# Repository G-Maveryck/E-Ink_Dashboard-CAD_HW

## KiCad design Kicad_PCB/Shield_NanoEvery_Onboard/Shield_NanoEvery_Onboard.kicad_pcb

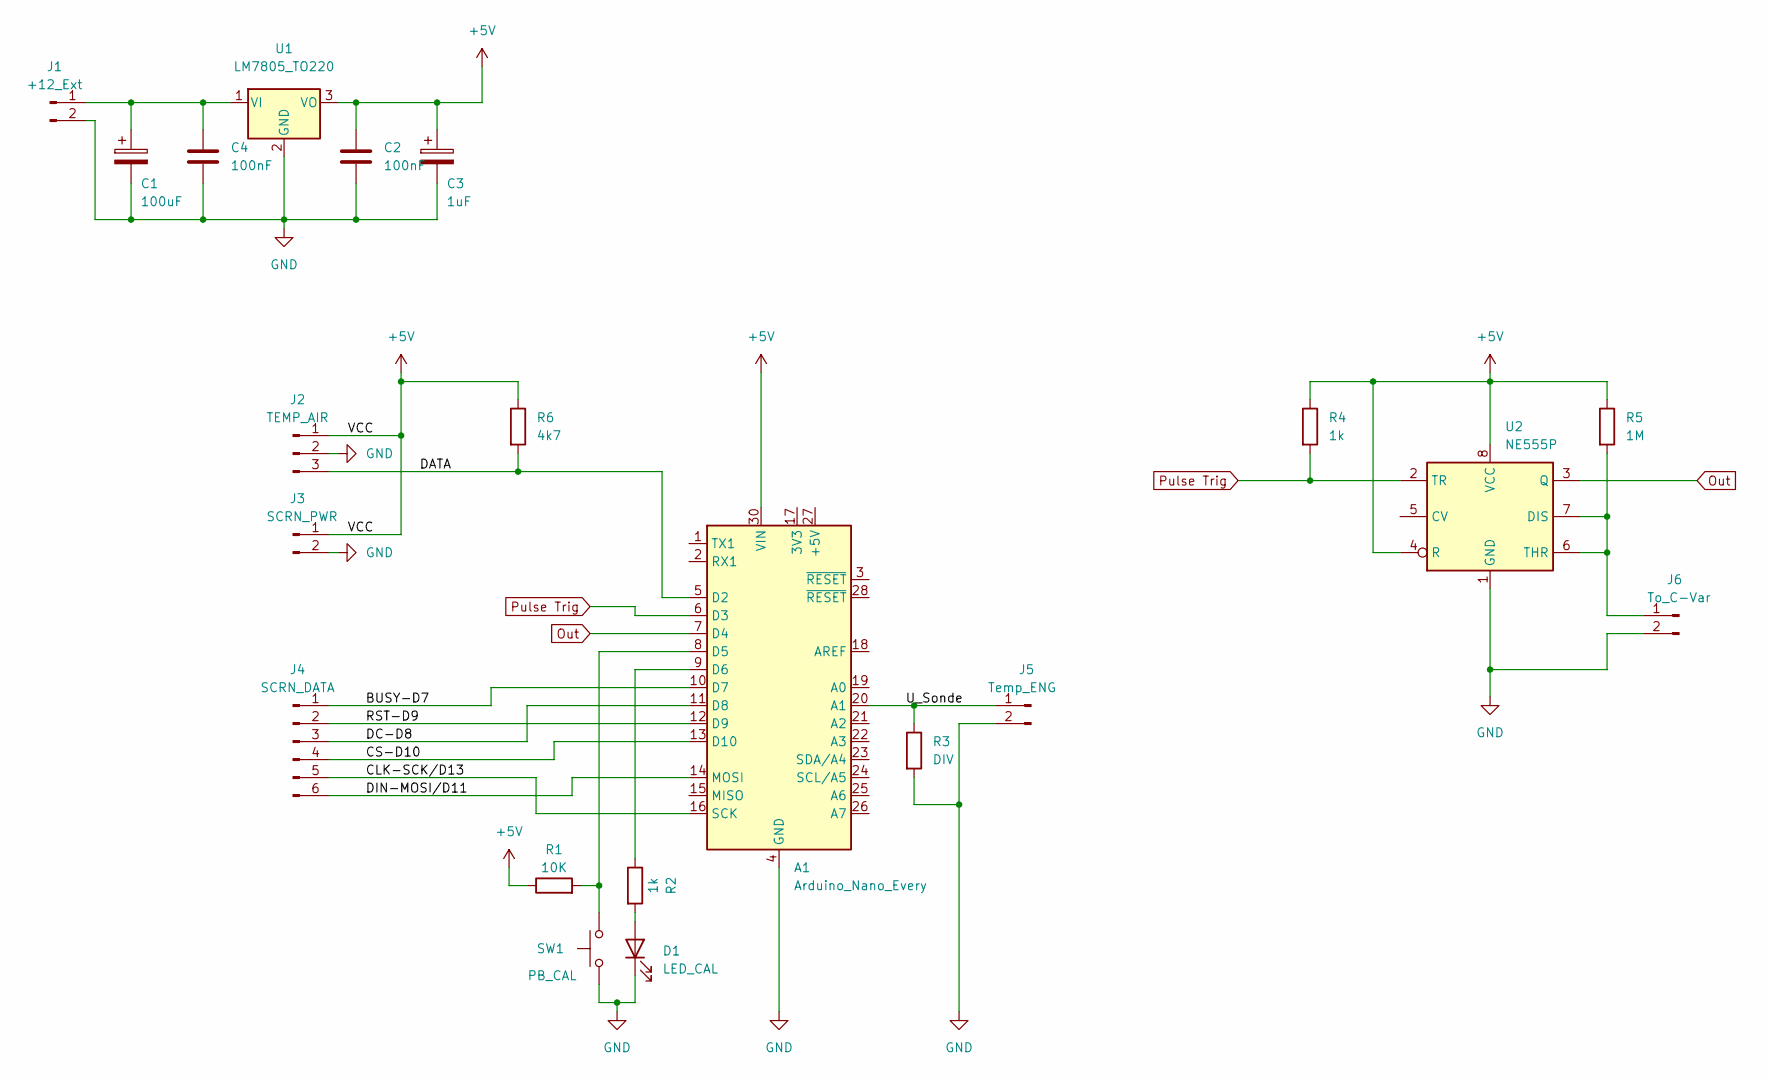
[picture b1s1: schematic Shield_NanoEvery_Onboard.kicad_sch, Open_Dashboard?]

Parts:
A1: Arduino_Nano_Every; Arduino_Nano
C1: 100uF; CP_Radial_D7.5mm_P2.50mm
C2, C4: 100nF; C_Disc_D4.3mm_W1.9mm_P5.00mm
C3: 1uF; CP_Radial_D5.0mm_P2.50mm
D1: LED_CAL; LED_D3.0mm
J1: +12_Ext; PinHeader_1x02_P2.54mm_Vertical
J2: TEMP_AIR; PinHeader_1x03_P2.54mm_Vertical
J3: SCRN_PWR; PinHeader_1x02_P2.54mm_Vertical
J4: SCRN_DATA; PinHeader_1x06_P2.54mm_Vertical
J5: Temp_ENG; PinHeader_1x02_P2.54mm_Vertical
J6: To_C-Var; PinHeader_1x02_P2.54mm_Vertical
R1: 10K; R_Axial_DIN0207_L6.3mm_D2.5mm_P7.62mm_Horizontal
R2, R4: 1k; R_Axial_DIN0207_L6.3mm_D2.5mm_P7.62mm_Horizontal
R3: DIV; R_Axial_DIN0207_L6.3mm_D2.5mm_P7.62mm_Horizontal
R5: 1M; R_Axial_DIN0207_L6.3mm_D2.5mm_P7.62mm_Horizontal
R6: 4k7; R_Axial_DIN0207_L6.3mm_D2.5mm_P7.62mm_Horizontal
SW1: PB_CAL; SW_PUSH_6mm_H4.3mm
U1: LM7805_TO220; TO-220-3_Vertical
U2: NE555P; DIP-8_W7.62mm

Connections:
+5V: A1.30 (VIN), C2.1, C3.1, J2.1, J3.1, R1.1, R4.1, R5.1, R6.1, U1.3 (VO), U2.4 (R), U2.8 (VCC)
/BUSY-D7: A1.10 (D7), J4.1
/CLK-SCK/D13: A1.16 (SCK), J4.5
/CS-D10: A1.13 (D10), J4.4
/DATA: A1.5 (D2), J2.3, R6.2
/DC-D8: A1.11 (D8), J4.3
/DIN-MOSI/D11: A1.14 (MOSI), J4.6
/RST-D9: A1.12 (D9), J4.2
/U_Sonde: A1.20 (A1), J5.1, R3.1
GND: A1.4 (GND), A1.29 (GND), C1.2, C2.2, C3.2, C4.2, D1.1 (K), J1.2, J2.2, J3.2, J5.2, J6.2, R3.2, SW1.1, U1.2 (GND), U2.1 (GND)
unnamed: A1.8 (D5), R1.2, SW1.2
unnamed: A1.9 (D6), R2.1
unnamed: C1.1, C4.1, J1.1, U1.1 (VI)
unnamed: D1.2 (A), R2.2
unnamed: J6.1, R5.2, U2.6 (THR), U2.7 (DIS)
Out: A1.7 (D4), U2.3 (Q)
Pulse Trig: A1.6 (D3), R4.2, U2.2 (TR)

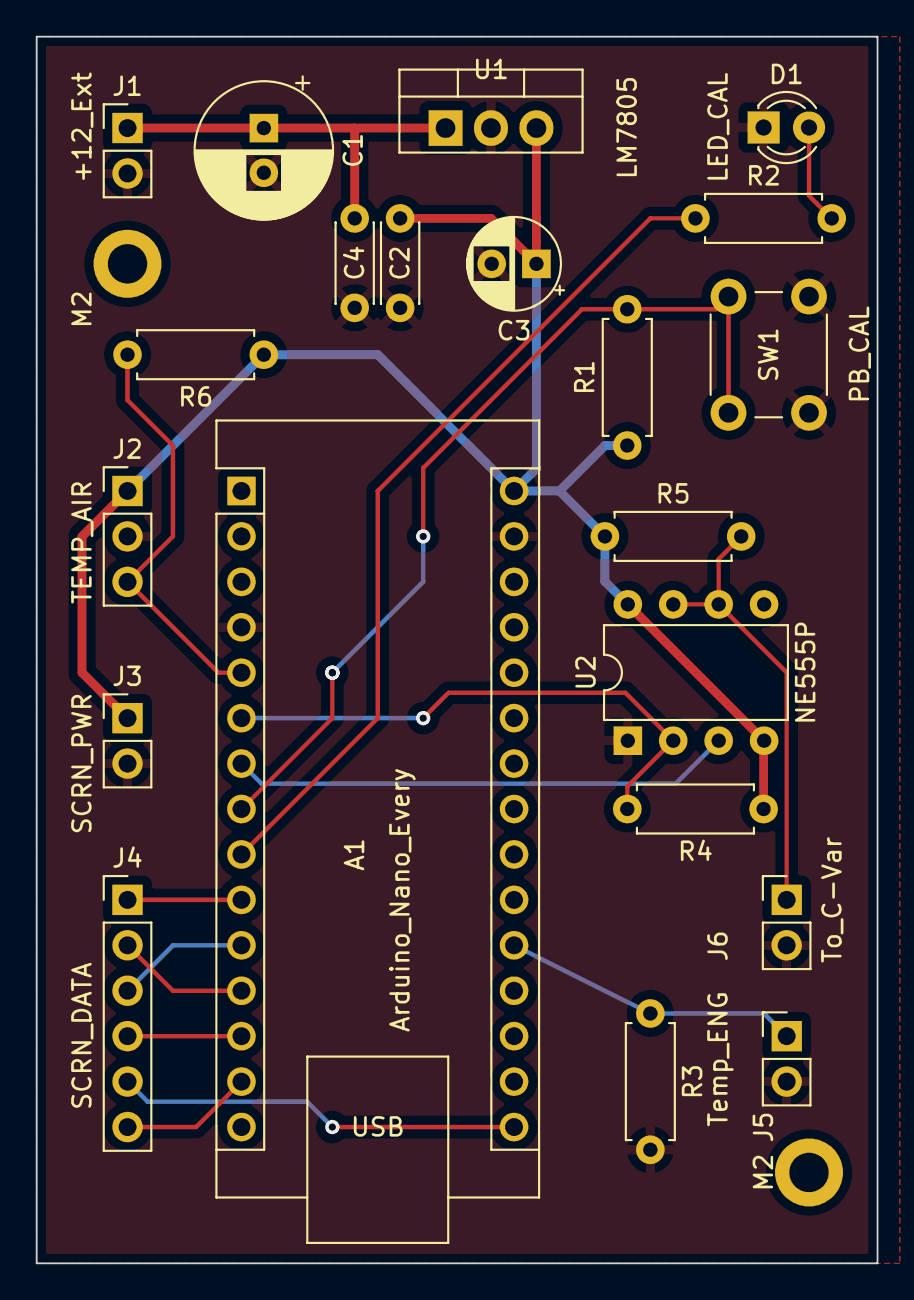
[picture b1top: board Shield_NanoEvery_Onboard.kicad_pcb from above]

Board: 2 copper layers, 47.0 x 68.6 mm, 23 parts (0 on the bottom side), 17 nets.

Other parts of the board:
M2, M2#2: M2; MountingHole_2.2mm_M2_DIN965_Pad

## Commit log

2023-06-09 Initial Commit
    Cad files for Electronic box, screen case, jauge hardware parts and PCB Cad filles
2023-06-11 Updated file structure
2023-06-13 Modified files structure, add dir for STEP&STL
2023-06-15 Added STL files
2023-07-06 Fixed M2/3 insert margin
2023-07-29 Modified height of Arduino box to fit electronics
2023-07-29 Added fixing holes outside the Arduino Box
2023-12-18 Reduced insert hole size for SLA Printing

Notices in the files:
Kicad_PCB/Shield_NanoEvery_Onboard/Shield_NanoEvery_Onboard.kicad_sch:
Distributed under Gnu GPL-3
